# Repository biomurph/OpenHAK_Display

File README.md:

# OpenHAK_Display
Add an  OLED Display To Your OpenHAK!

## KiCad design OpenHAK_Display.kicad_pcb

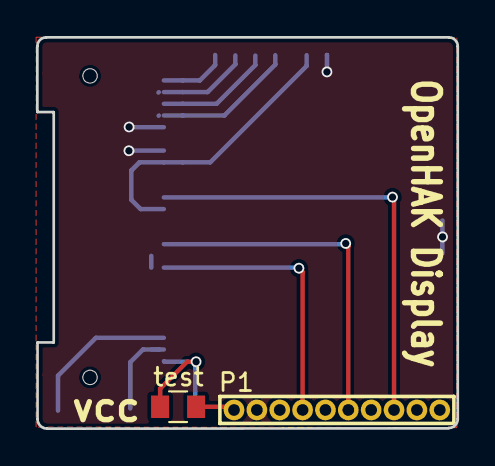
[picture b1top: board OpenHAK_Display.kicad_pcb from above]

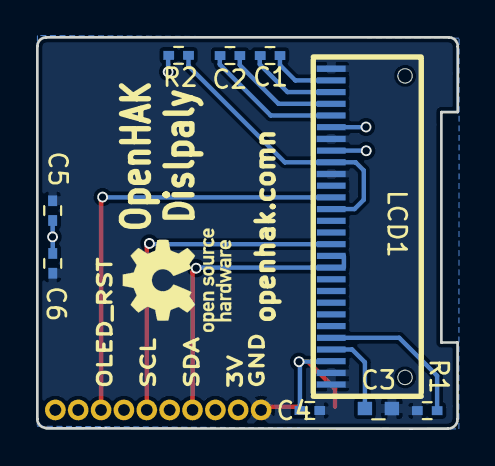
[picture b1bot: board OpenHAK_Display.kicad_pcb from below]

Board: 2 copper layers, 23.4 x 21.7 mm, 11 parts (9 on the bottom side), 13 nets.

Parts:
C1, C2, C5: 1uF; C_0402
C3: 4.7uF 16V; C_0603
C4: 2.2uF; C_0402
C6: 0.1uF; C_0402
LCD1: OLED_64x48; 0.66in_OLED_Display
P1: M52-Series_Male_TH_Harwin; M52-Series_M_TH_0.05_Harwin
R1: 390K; C_0402
R2: 10K; C_0402
test: TEST POINT; C_0805

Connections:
+3V3: C5.1, C6.1, LCD1.6, LCD1.8, P1.2, R2.1
/OLED_RST: LCD1.12, P1.8
/SCL: LCD1.16, P1.6
/SDA: LCD1.17, LCD1.18, P1.4
/VCC: C4.1, LCD1.26, test.1
GND: C3.1, C4.2, C5.2, C6.2, LCD1.1, LCD1.7, LCD1.10, LCD1.27, LCD1.28, P1.1, R1.2, test.2
unnamed: C1.1, LCD1.2
unnamed: C1.2, LCD1.3
unnamed: C2.1, LCD1.4
unnamed: C2.2, LCD1.5
unnamed: C3.2, LCD1.25
unnamed: LCD1.9, LCD1.13, R2.2
unnamed: LCD1.24, R1.1

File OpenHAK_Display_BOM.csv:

"Id";"Designator";"Package";"Quantity";"Designation";"Supplier and ref";
1;"C1,C2,C5";"C_0603";3;"1uF";;;
2;"C3";"C_0603";1;"4.7uF 16V";;;
3;"C4";"C_0603";1;"2.2uF";;;
4;"C6";"C_0603";1;"0.1uF";;;
5;"LCD1";"0.66in_OLED_Display";1;"OLED_64x48";;;
6;"P1";"Pin_Header_Straight_1x08_Pitch1.00mm";1;"CONN_01X08";;;
7;"R1";"C_0603";1;"390K";;;
8;"R2";"C_0603";1;"10K";;;

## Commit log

2018-01-21 Initial Commit with bare KiCad file structure
2018-01-21 Scematic update
2018-01-23 Added decoupling caps, component rating
2018-01-30 made PCB layout
    done-ish
2018-02-01 added simple BOM
2018-02-11 Connect pin 17 to pin 18 to make it work
2019-05-06 redesign layout for new hardware
2019-05-06 swapped 0603 for 0402
2019-05-06 repackaged library
2019-06-16 updating layout to fit beta board
2019-06-17 Adjusting to fit the new 10 pin breakout
2019-06-17 removed ignored files
2019-06-17 cleaned up silk and made production files
2019-06-18 made production files
2019-06-19 updated paad size for header
2019-06-19 resized the annular ring on the 1.27mm header row
2019-06-24 updating beta branch
2019-06-24 changed tx rx on schematics
2019-06-24 updated layout of BETA Display branch
2019-07-22 edits in silk
2019-07-24 moved silk inside board outline
2020-09-15 cleaned up libraries
